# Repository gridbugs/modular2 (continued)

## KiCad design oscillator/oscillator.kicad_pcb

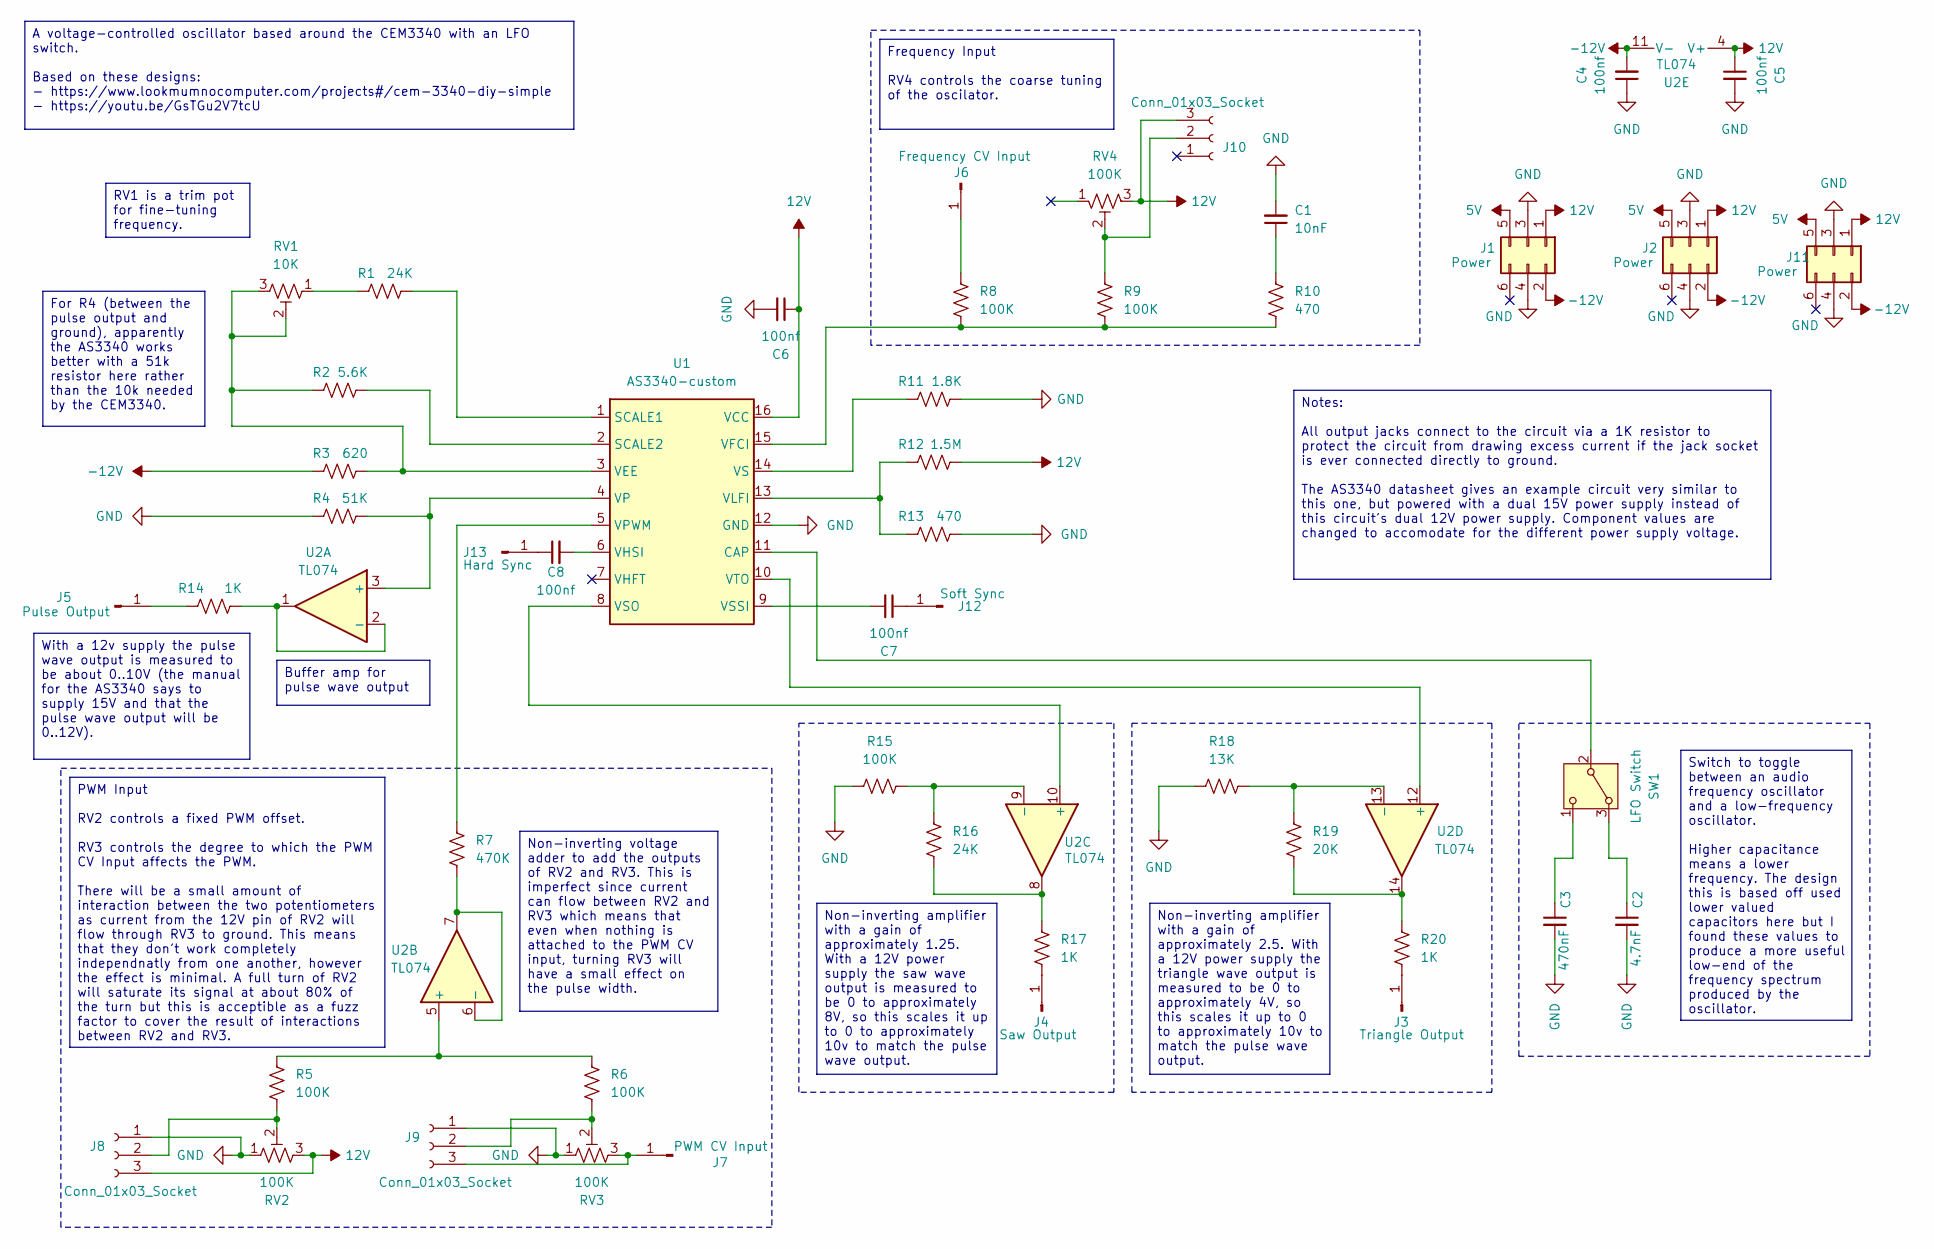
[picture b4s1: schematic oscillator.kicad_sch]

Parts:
C1: 10nF; C_Disc_D5.0mm_W2.5mm_P5.00mm
C2: 4.7nF; C_Disc_D5.0mm_W2.5mm_P5.00mm
C3: 470nF; C_Disc_D5.0mm_W2.5mm_P5.00mm
C4, C5, C6, C7, C8: 100nf; C_Disc_D4.3mm_W1.9mm_P5.00mm
J1, J2, J11: Power; IDC-Header_2x03_P2.54mm_Vertical
J3: Triangle Output; banana-jack
J4: Saw Output; banana-jack
J5: Pulse Output; banana-jack
J6: Frequency CV Input; banana-jack
J7: PWM CV Input; banana-jack
J8, J9, J10: Conn_01x03_Socket; pot
J12: Soft Sync; banana-jack
J13: Hard Sync; banana-jack
R1, R16: 24K; R_Axial_DIN0207_L6.3mm_D2.5mm_P10.16mm_Horizontal
R2: 5.6K; R_Axial_DIN0207_L6.3mm_D2.5mm_P10.16mm_Horizontal
R3: 620; R_Axial_DIN0207_L6.3mm_D2.5mm_P10.16mm_Horizontal
R4: 51K; R_Axial_DIN0207_L6.3mm_D2.5mm_P10.16mm_Horizontal
R5, R6, R8, R9, R15: 100K; R_Axial_DIN0207_L6.3mm_D2.5mm_P10.16mm_Horizontal
R7: 470K; R_Axial_DIN0207_L6.3mm_D2.5mm_P10.16mm_Horizontal
R10, R13: 470; R_Axial_DIN0207_L6.3mm_D2.5mm_P10.16mm_Horizontal
R11: 1.8K; R_Axial_DIN0207_L6.3mm_D2.5mm_P10.16mm_Horizontal
R12: 1.5M; R_Axial_DIN0207_L6.3mm_D2.5mm_P10.16mm_Horizontal
R14, R17, R20: 1K; R_Axial_DIN0207_L6.3mm_D2.5mm_P10.16mm_Horizontal
R18: 13K; R_Axial_DIN0207_L6.3mm_D2.5mm_P10.16mm_Horizontal
R19: 20K; R_Axial_DIN0207_L6.3mm_D2.5mm_P10.16mm_Horizontal
RV1: 10K; Potentiometer_Bourns_3296W_Vertical
RV2, RV3, RV4: 100K; pot-socket
SW1: LFO Switch; switch1
U1: AS3340-custom; DIP-16_W7.62mm_Socket
U2: TL074; DIP-14_W7.62mm_Socket

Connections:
5V: J1.5, J2.5, J11.5
12V: C5.1, C6.1, J1.1, J2.1, J8.3, J10.3, J11.1, R12.2, RV2.3, RV4.3, U1.16 (VCC), U2.4 (V+)
-12V: C4.2, J1.2, J2.2, J11.2, R3.1, U2.11 (V-)
GND: C1.2, C2.2, C3.2, C4.1, C5.2, C6.2, J1.3, J1.4, J2.3, J2.4, J8.1, J9.1, J11.3, J11.4, R4.1, R11.2, R13.2, R15.1, R18.1, RV2.1, RV3.1, U1.12 (GND)
unnamed: C1.1, R10.1
unnamed: J3.1, R20.2
unnamed: J4.1, R17.2
unnamed: J5.1, R14.1
unnamed: J6.1, R8.1
unnamed: J7.1, J9.3, RV3.3
unnamed: J8.2, R5.2, RV2.2
unnamed: J9.2, R6.2, RV3.2
unnamed: J10.2, R9.1, RV4.2
unnamed: C7.1, J12.1
unnamed: C8.1, J13.1
unnamed: R1.1, RV1.1
unnamed: R16.2, R17.1, U2.8
unnamed: R19.2, R20.1, U2.14
unnamed: C2.1, SW1.3 (A)
unnamed: SW1.2 (B), U1.11 (CAP)
unnamed: C3.1, SW1.1 (C)
unnamed: R1.2, U1.1 (SCALE1)
unnamed: R2.2, U1.2 (SCALE2)
unnamed: R2.1, R3.2, RV1.2, RV1.3, U1.3 (VEE)
unnamed: R8.2, R9.2, R10.2, U1.15 (VFCI)
unnamed: C8.2, U1.6 (VHSI)
unnamed: R12.1, R13.1, U1.13 (VLFI)
unnamed: R4.2, U1.4 (VP), U2.3 (+)
unnamed: R7.1, U1.5 (VPWM)
unnamed: R11.1, U1.14 (VS)
unnamed: U1.8 (VSO), U2.10 (+)
unnamed: C7.2, U1.9 (VSSI)
unnamed: U1.10 (VTO), U2.12 (+)
unnamed: R14.2, U2.1, U2.2 (-)
unnamed: R5.1, R6.1, U2.5 (+)
unnamed: R7.2, U2.6 (-), U2.7
unnamed: R15.2, R16.1, U2.9 (-)
unnamed: R18.2, R19.1, U2.13 (-)

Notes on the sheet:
Notes: All output jacks connect to the circuit via a 1K resistor to protect the circuit from drawing excess current if the jack socket is ever connected directly to ground. The AS3340 datasheet gives an example circuit very similar to this one, but powered with a dual 15V power supply instead of th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
Switch to toggle between an audio frequency oscillator and a low-frequency oscillator. Higher capacitance means a lower frequency. The design this is based off used lower valued capacitors here but I found these values to produce a more useful low-end of the frequency spectrum produced by the oscil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
With a 12v supply the pulse wave output is measured to be about 0..10V (the manual for the AS3340 says to supply 15V and that the pulse wave output will be 0..12V).
Frequency Input RV4 controls the coarse tuning of the oscilator.
RV1 is a trim pot for fine-tuning frequency.
Non-inverting amplifier with a gain of approximately 1.25. With a 12V power supply the saw wave output is measured to be 0 to approximately 8V, so this scales it up to 0 to approximately 10v to match the pulse wave output.
For R4 (between the pulse output and ground), apparently the AS3340 works better with a 51k resistor here rather than the 10k needed by the CEM3340.
A voltage-controlled oscillator based around the CEM3340 with an LFO switch. Based on these designs: - https://www.lookmumnocomputer.com/projects#/cem-3340-diy-simple - https://youtu.be/GsTGu2V7tcU
Non-inverting voltage adder to add the outputs of RV2 and RV3. This is imperfect since current can flow between RV2 and RV3 which means that even when nothing is attached to the PWM CV input, turning RV3 will have a small effect on the pulse width.
Non-inverting amplifier with a gain of approximately 2.5. With a 12V power supply the triangle wave output is measured to be 0 to approximately 4V, so this scales it up to 0 to approximately 10v to match the pulse wave output.
Buffer amp for pulse wave output
PWM Input RV2 controls a fixed PWM offset. RV3 controls the degree to which the PWM CV Input affects the PWM. There will be a small amount of interaction between the two potentiometers as current from the 12V pin of RV2 will flow through RV3 to ground. This means that they don't work completely ind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

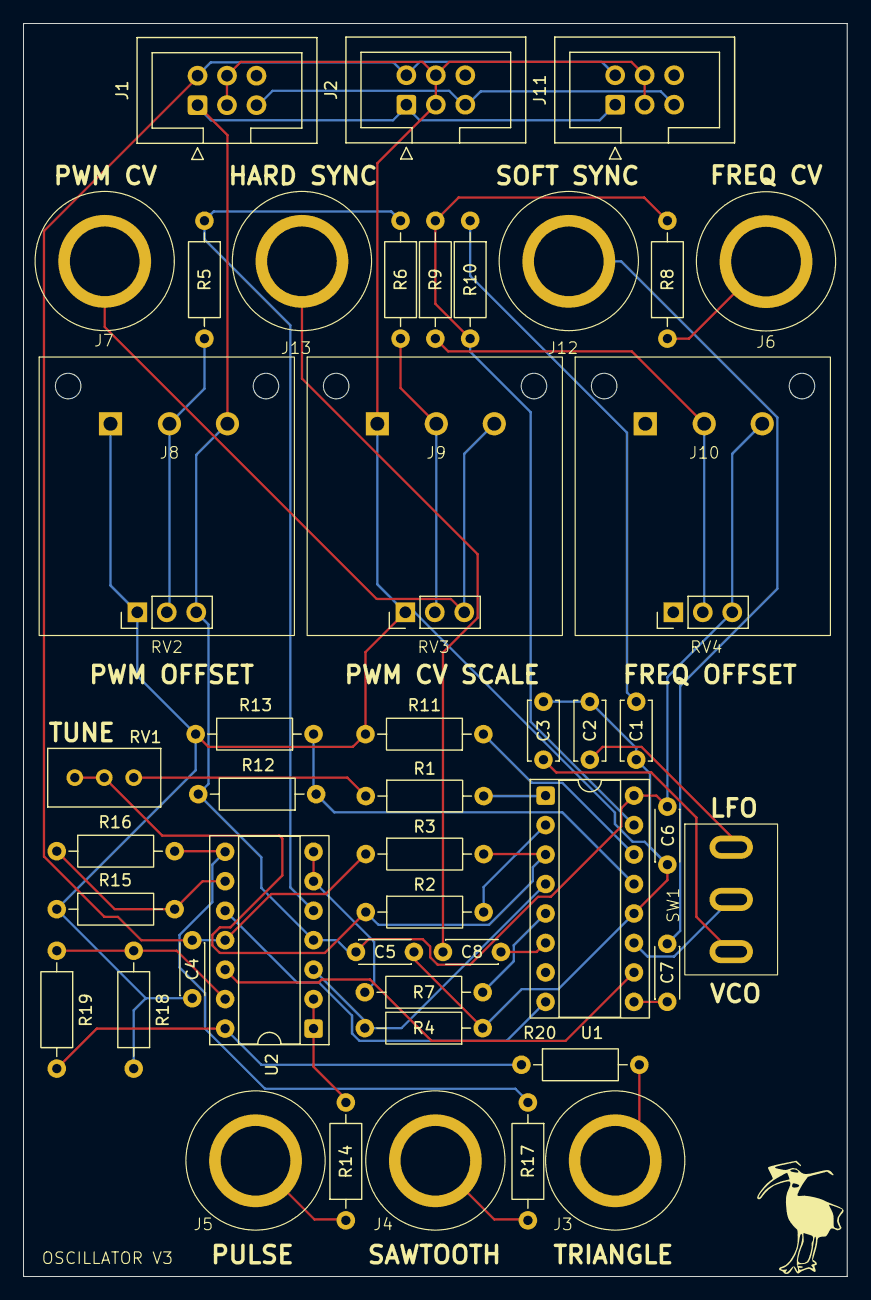
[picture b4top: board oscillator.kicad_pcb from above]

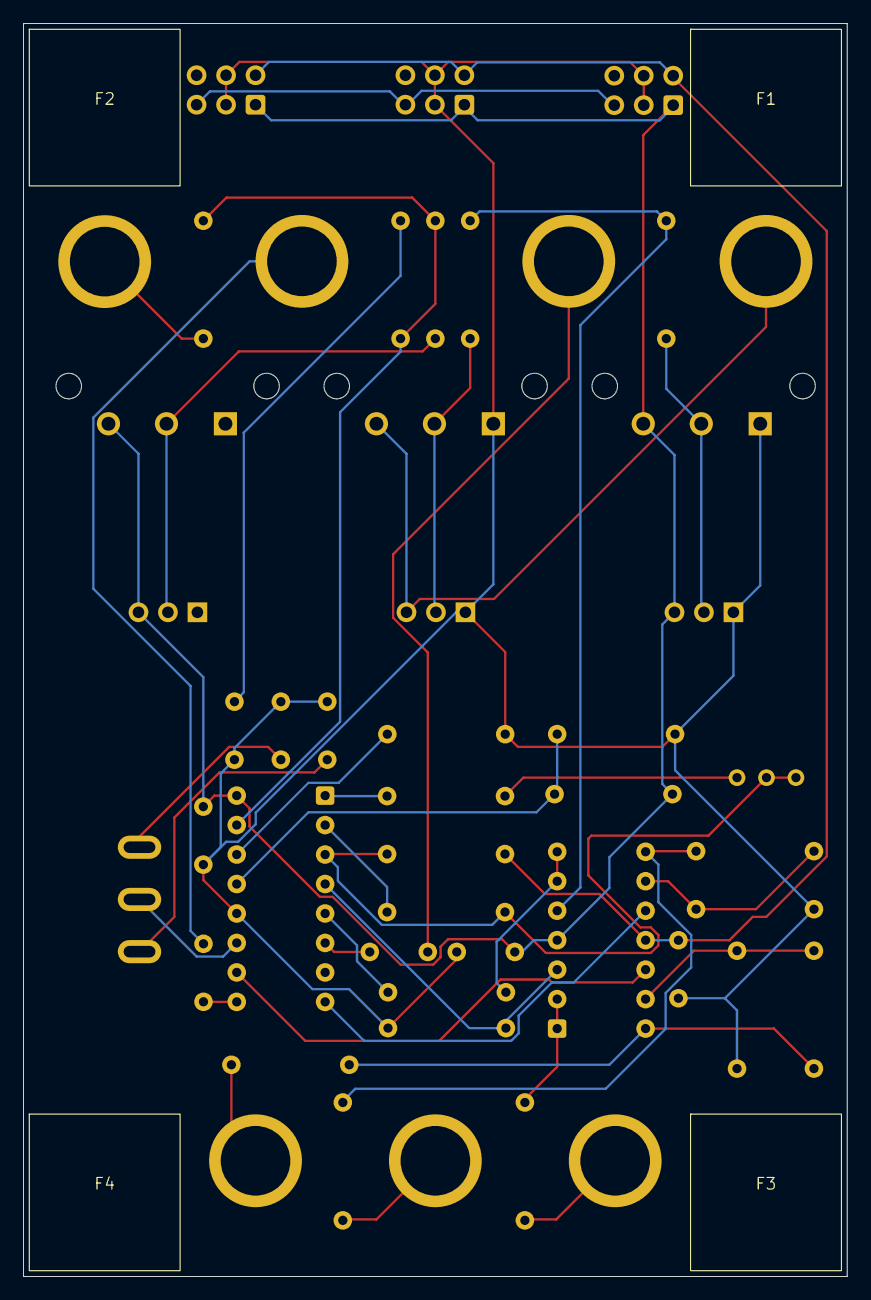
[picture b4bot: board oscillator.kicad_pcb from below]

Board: 2 copper layers, 71.0 x 108.0 mm, 52 parts (4 on the bottom side), 38 nets.

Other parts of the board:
F1, F2, F3, F4: foot

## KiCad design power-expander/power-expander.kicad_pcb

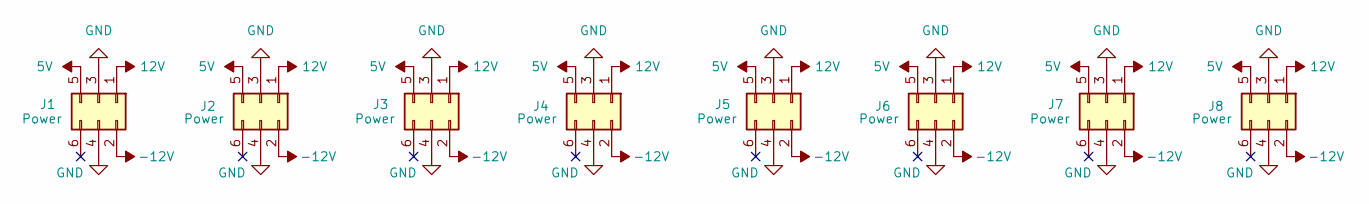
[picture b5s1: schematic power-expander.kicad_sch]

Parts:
J1, J2, J3, J4, J5, J6, J7, J8: Power; IDC-Header_2x03_P2.54mm_Vertical

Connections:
5V: J1.5, J2.5, J3.5, J4.5, J5.5, J6.5, J7.5, J8.5
12V: J1.1, J2.1, J3.1, J4.1, J5.1, J6.1, J7.1, J8.1
-12V: J1.2, J2.2, J3.2, J4.2, J5.2, J6.2, J7.2, J8.2
GND: J1.3, J1.4, J2.3, J2.4, J3.3, J3.4, J4.3, J4.4, J5.3, J5.4, J6.3, J6.4, J7.3, J7.4, J8.3, J8.4

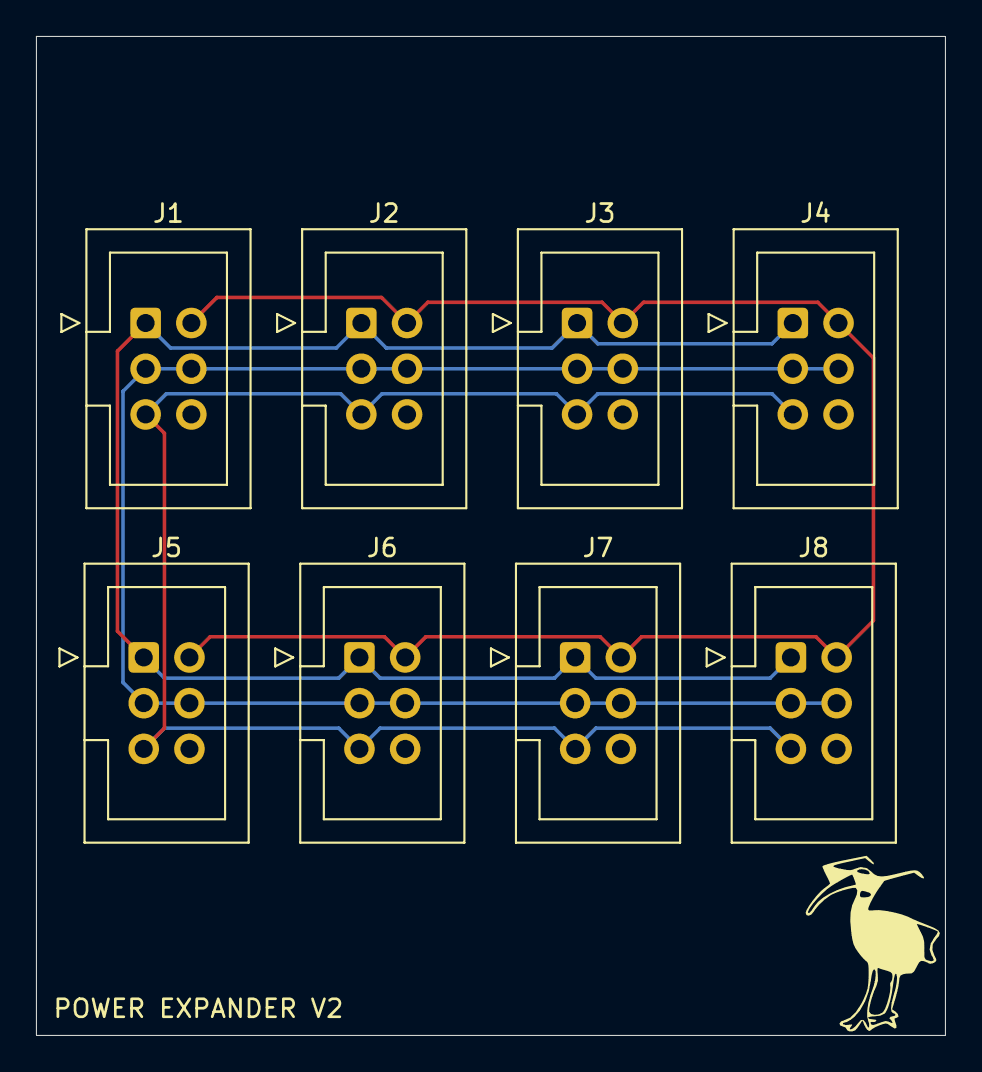
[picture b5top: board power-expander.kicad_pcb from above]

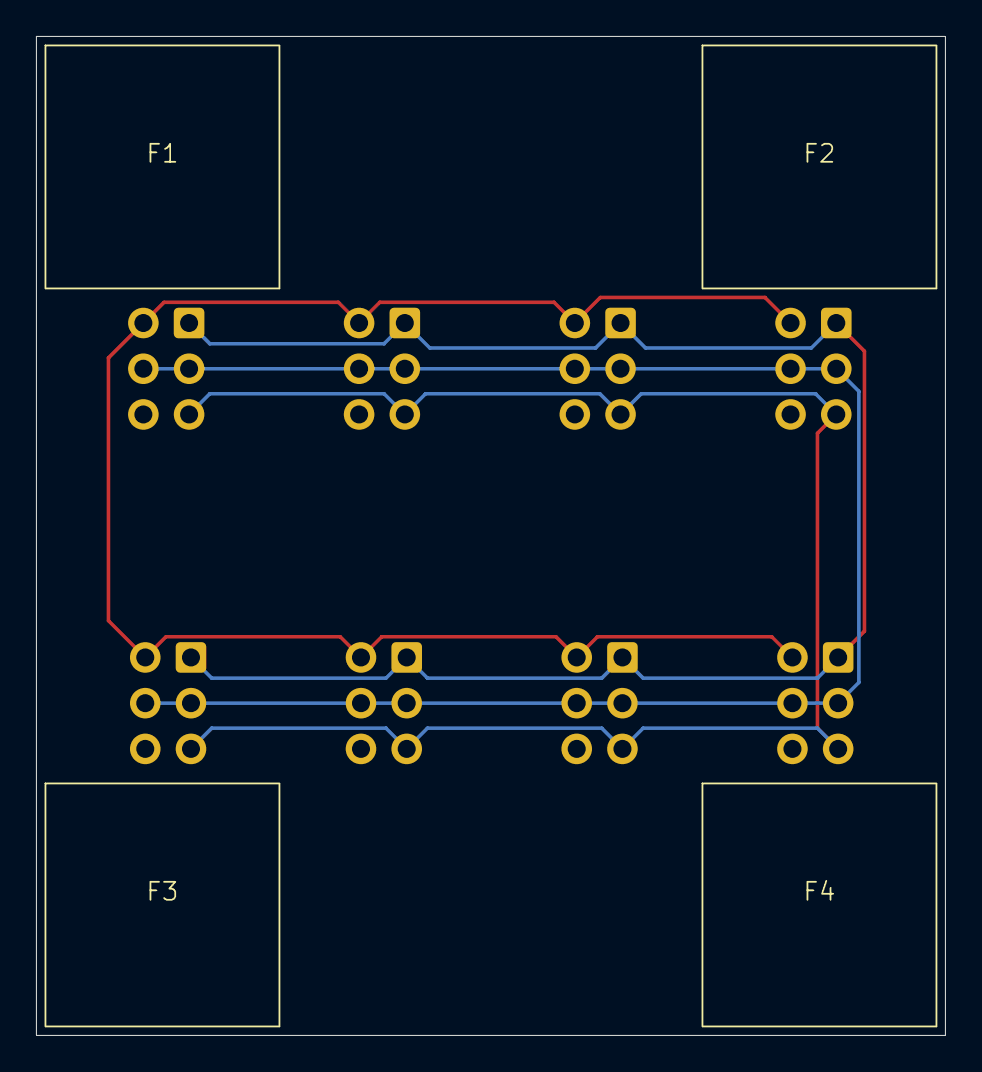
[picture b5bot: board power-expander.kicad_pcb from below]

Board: 2 copper layers, 50.5 x 55.5 mm, 12 parts (4 on the bottom side), 4 nets.

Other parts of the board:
F1, F2, F3, F4: foot

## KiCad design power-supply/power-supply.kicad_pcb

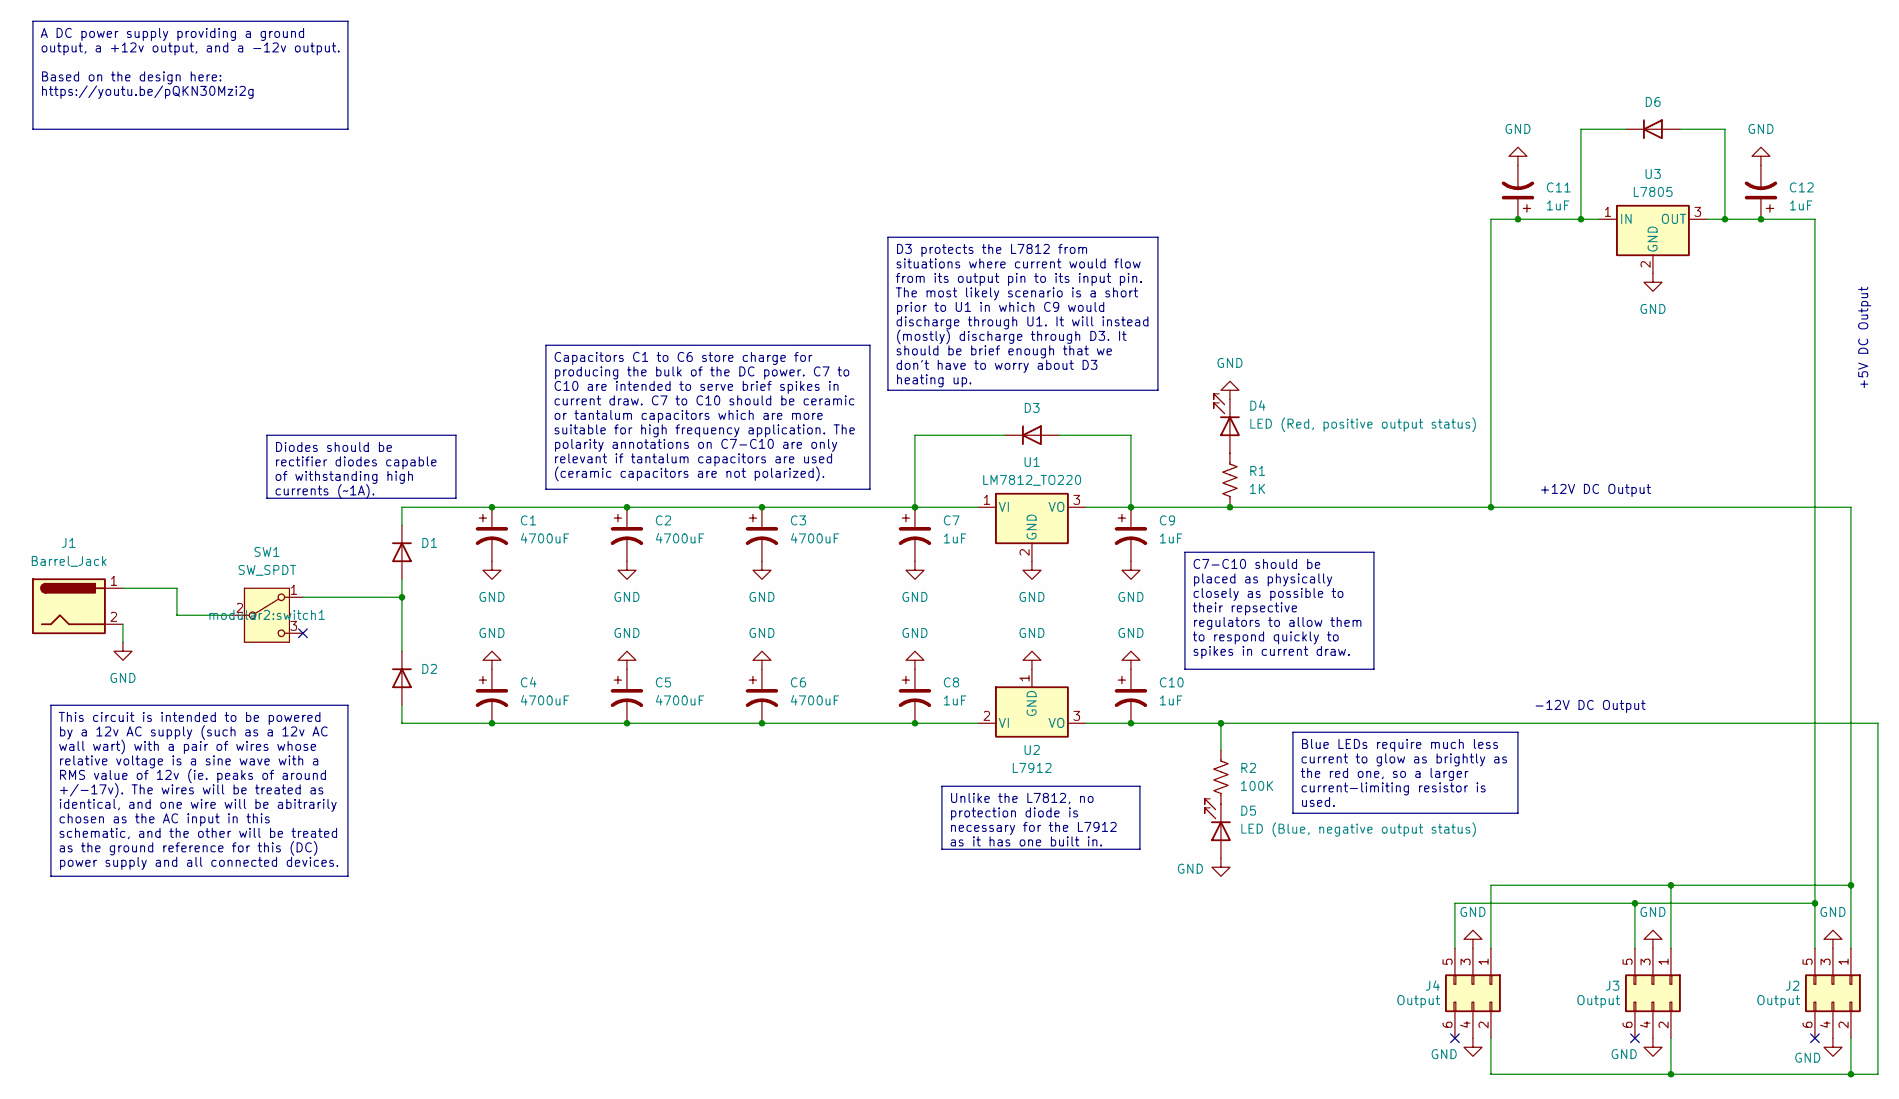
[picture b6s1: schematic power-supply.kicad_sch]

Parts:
C1, C2, C3, C4, C5, C6: 4700uF; CP_Radial_D18.0mm_P7.50mm
C7, C8, C9, C10, C11, C12: 1uF; CP_Radial_Tantal_D4.5mm_P2.50mm
D1, D2, D3, D6: Rectifier Diode; D_A-405_P7.62mm_Horizontal
D4: LED (Red, positive output status); LED_D5.0mm
D5: LED (Blue, negative output status); LED_D5.0mm
J1: Barrel_Jack; BarrelJack_GCT_DCJ200-10-A_Horizontal
J2, J3, J4: Output; IDC-Header_2x03_P2.54mm_Vertical
R1: 1K; R_Axial_DIN0207_L6.3mm_D2.5mm_P10.16mm_Horizontal
R2: 100K; R_Axial_DIN0207_L6.3mm_D2.5mm_P10.16mm_Horizontal
SW1: SW_SPDT; switch1
U1: LM7812_TO220; TO-220-3_Vertical
U2: L7912; TO-220-3_Vertical
U3: L7805; TO-220-3_Vertical

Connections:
GND: C1.2, C2.2, C3.2, C4.1, C5.1, C6.1, C7.2, C8.1, C9.2, C10.1, C11.2, C12.2, D4.1 (K), D5.2 (A), J1.2, J2.3, J2.4, J3.3, J3.4, J4.3, J4.4, U1.2 (GND), U2.1 (GND), U3.2 (GND)
unnamed: D1.2 (A), D2.1 (K), SW1.1 (A)
unnamed: C1.1, C2.1, C3.1, C7.1, D1.1 (K), D3.1 (K), U1.1 (VI)
unnamed: C4.2, C5.2, C6.2, C8.2, D2.2 (A), U2.2 (VI)
unnamed: C9.1, C11.1, D3.2 (A), D6.1 (K), J2.1, J3.1, J4.1, R1.2, U1.3 (VO), U3.1 (IN)
unnamed: D4.2 (A), R1.1
unnamed: D5.1 (K), R2.2
unnamed: C12.1, D6.2 (A), J2.5, J3.5, J4.5, U3.3 (OUT)
unnamed: C10.2, J2.2, J3.2, J4.2, R2.1, U2.3 (VO)
unnamed: J1.1, SW1.2 (B)

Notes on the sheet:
-12V DC Output
+12V DC Output
+5V DC Output
D3 protects the L7812 from situations where current would flow from its output pin to its input pin. The most likely scenario is a short prior to U1 in which C9 would discharge through U1. It will instead (mostly) discharge through D3. It should be brief enough that we don't have to worry about D3 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
Blue LEDs require much less current to glow as brightly as the red one, so a larger current-limiting resistor is used.
Unlike the L7812, no protection diode is necessary for the L7912 as it has one built in.
A DC power supply providing a ground output, a +12v output, and a -12v output. Based on the design here: https://youtu.be/pQKN30Mzi2g
This circuit is intended to be powered by a 12v AC supply (such as a 12v AC wall wart) with a pair of wires whose relative voltage is a sine wave with a RMS value of 12v (ie. peaks of around +/-17v). The wires will be treated as identical, and one wire will be abitrarily chosen as the AC input in t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
Diodes should be rectifier diodes capable of withstanding high currents (~1A).
C7-C10 should be placed as physically closely as possible to their repsective regulators to allow them to respond quickly to spikes in current draw.
Capacitors C1 to C6 store charge for producing the bulk of the DC power. C7 to C10 are intended to serve brief spikes in current draw. C7 to C10 should be ceramic or tantalum capacitors which are more suitable for high frequency application. The polarity annotations on C7-C10 are only relevant if t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

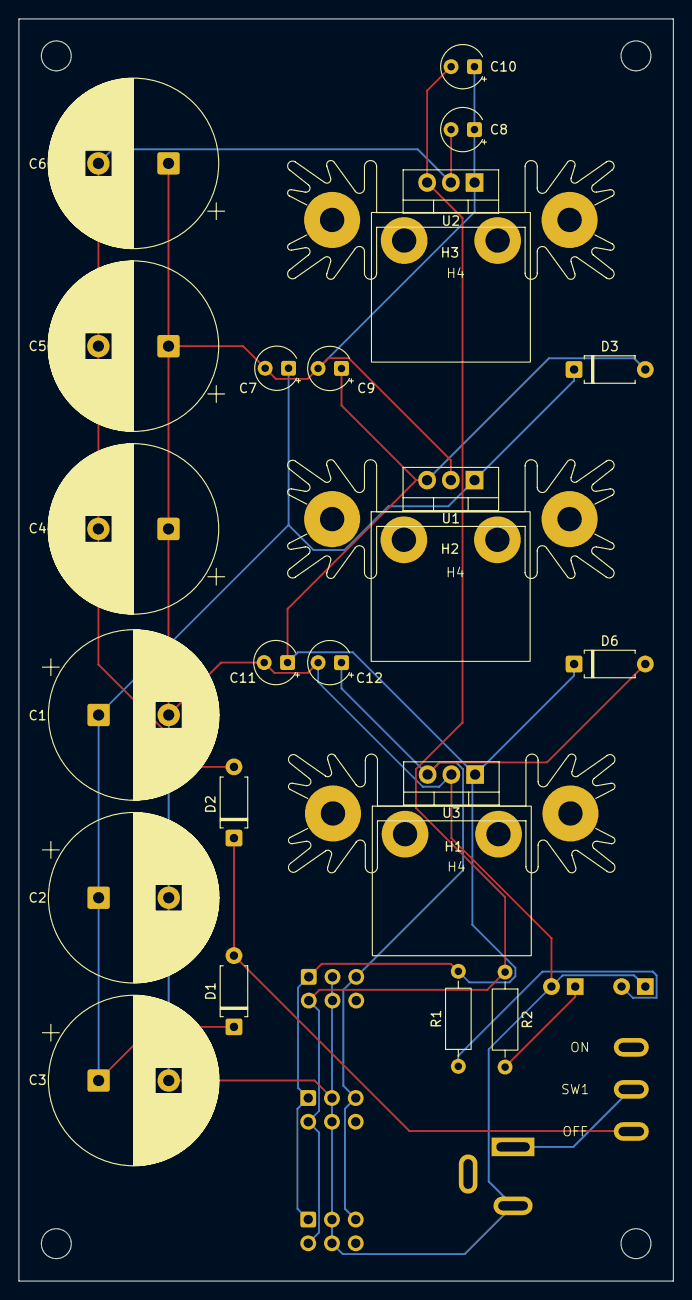
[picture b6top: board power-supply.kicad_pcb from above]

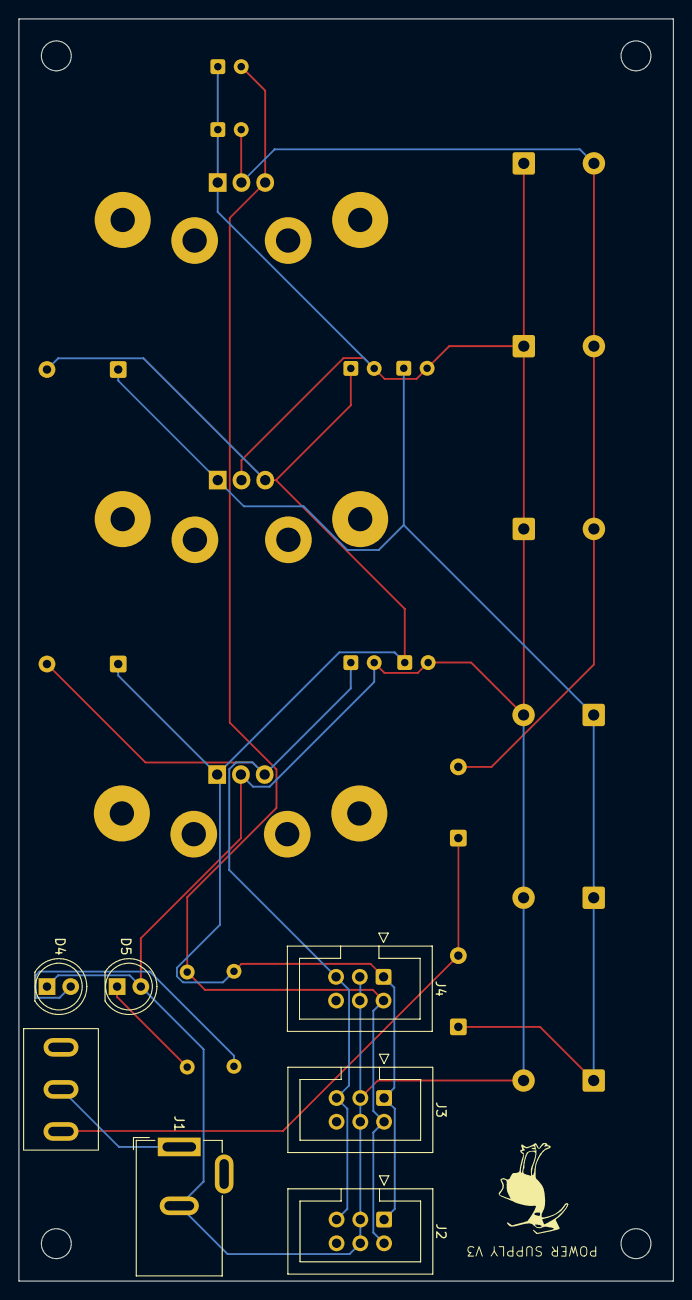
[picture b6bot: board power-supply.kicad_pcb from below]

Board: 2 copper layers, 70.0 x 135.0 mm, 34 parts (7 on the bottom side), 10 nets.

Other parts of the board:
H1, H2, H3: Heatsink_AAVID_Extruded_531002B02100G_34.9x12.7mm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; Heatsink_AAVID_Extruded_531002B02100G_34.9x12.7mm_H25.4mm
H4, H4#2, H4#3: heatsink to220
